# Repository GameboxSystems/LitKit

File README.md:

# LitKit

LitKit is a tiny little Attiny85 addressable RGB LED board that features only three required parts to be funtional: Attiny85, 0.1uF cermaic 0805 cap, and a 100 ohm 0805 resistor. That's all!

Also features WS2812B 3535 on PCB, V+/GND/Data to daisy chain WS2812B LEDs to the main board, and solder pads for connecting a button.

To flash the board simply place the populated board on top a USBTinyISP boards ISP port, press down to ensure contact and flash! ISP Programming holes are measured to tension fit LitKit in place when pressed into place.

## Getting Started

### Prerequisites
Required:

* Populated LitKit Board
* Arduino IDE
* USBTinyISP Board
	* [Board tested working can be found here](https://www.ebay.com/itm/USB-Tiny-AVR-5V-ATtiny44-USBTinyISP-Programmer-For-Arduino-Bootloader/183986605082?hash=item2ad674cc1a:g:sEQAAOSwufJdm9h0) 

Recommended:

* 500mA + 3.3v-5v power source
* Any type of Addressable WS2812B LED array (Neopixel, LED strip, etc.)
* [Adafruit Neopixel Arduino Library](https://github.com/adafruit/Adafruit_NeoPixel)

## Software setup

* Install Arduino IDE (Tested with Arduino up to 1.8.13 from arduino.cc)
* Install TinyISP driver from https://learn.adafruit.com/usbtinyisp/download
* Open Arduino IDE
* Open File->Preferences
* Add https://raw.githubusercontent.com/damellis/attiny/ide-1.6.x-boards-manager/package_damellis_attiny_index.json to "Additional Boards Manager URLs"
* Run Tools->Board->Boards Manager
* Install "attiny" board package
* Select ATtiny25/45/85 at Tools->Board->ATtiny Microcontroller
* Select ATtiny85 at Tools->Board->Processor
* Select Internal 16 MHz at Tools->Clock
* Select USBtinyISP at Tools->Programmer

## Examples

* Example1 - Single WS2812B demo
* Example2 - WS6812B array demo
* Example3 - Single SK6812 demo

### Run as multi file arduino sketch

* Copy src/LitKit.c and src/LitKit.h to selected example folder
* Rename LitKit.c to LitKit.ino
* Open exampleX.ino in Arduino IDE

### Flashing LitKit with USBTinyISP

*COMING SOON*

### Daisy Chaining Litkit -> LED Array

*COMING SOON*

## Currently Known Issues

N/A

## Built With

* Eagle

## Versions

v1.0 - Initial release

## Contributing

Please feel free to issue a PR or edit code freely. Would love to have people contribute ideas!

## Authors

* **Postman** - *Engineer at Gamebox Systems*
* **Knk**

## License

This project is licensed under the GPL-3.0 license, see attached license for info.

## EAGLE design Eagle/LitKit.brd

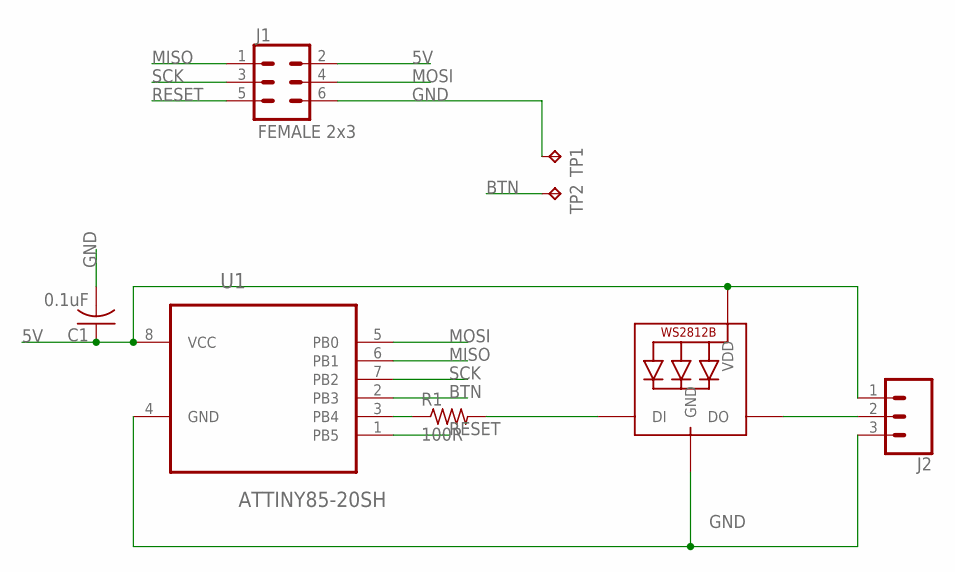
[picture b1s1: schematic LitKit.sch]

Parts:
C1: 0.1uF; C0805
J1: FEMALE 2x3; 2X3
J2: CONN_031X03_NO_SILK; 1X03_NO_SILK
LED1: WS2812B3535; LED3535
R1: 100R; R0805
TP1, TP2: TPB1,27; B1,27
U1: ATTINY85-20SH; SOIC127P798X216-8N

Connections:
5V: C1.1, J1.2, J2.1, LED1.2 (VDD), U1.8 (VCC)
BTN: TP2.TP, U1.2 (PB3)
GND: C1.2, J1.6, J2.3, LED1.4 (GND), TP1.TP, U1.4 (GND)
MISO: J1.1, U1.6 (PB1)
MOSI: J1.4, U1.5 (PB0)
unnamed: J2.2, LED1.3 (DO)
unnamed: R1.1, U1.3 (PB4)
unnamed: LED1.1 (DI), R1.2
RESET: J1.5, U1.1 (PB5)
SCK: J1.3, U1.7 (PB2)

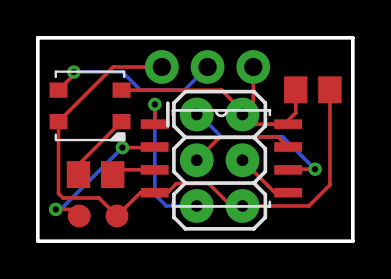
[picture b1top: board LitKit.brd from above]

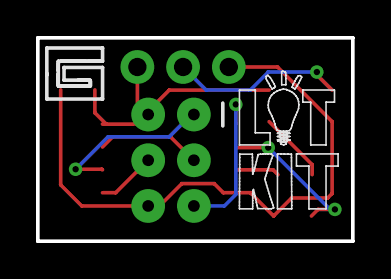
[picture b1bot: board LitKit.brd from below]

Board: 2 copper layers, 17.5 x 11.3 mm, 10 parts (2 on the bottom side), 10 nets.

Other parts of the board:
U$1: LITKIT
U$2: LKGB

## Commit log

2021-03-26 ATtiny85 code and Arduino configuration guide
2021-03-29 Multiple LEDs Control
2021-04-02 Comments and formating
2021-04-02 Load LEDs from array
2021-04-03 Documentation and image
2021-04-04 SK6812 support
2021-04-04 Examples description
2021-04-07 Tested with SK6812

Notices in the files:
parts and their libraries:
2x3PostStyle: Licensing: Creative Commons ShareAlike 4.0 International - https://creativecommons.org/licenses/by-sa/4.0
